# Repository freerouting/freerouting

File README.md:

<h1 align="center">Freerouting</h1>
<h5 align="center">Freerouting is an advanced autorouter for all PCB programs that support the standard Specctra or Electra DSN interface.</h5>

<p align="center">

</p>

<br/>

[**Download installers for Windows, Linux, and macOS here.**](https://github.com/freerouting/freerouting/releases)

> [!IMPORTANT]
> **Project Maintenance and Community Update**
>
> Dear fellow PCB designers and makers,
>
> I have been maintaining Freerouting since January 2020, and first and foremost, a heartfelt thank you to the active members of the community—your passion, contributions, and discussions are truly what keep me motivated.
>
> To be completely candid about my time and the project's funding: in the last 28 days alone, Freerouting had over 332,000 active users, but currently only 4 financial supporters, bringing in just $40 in donations. That is not enough to cover my monthly bills for the AI coding agents that power development, and I will continue paying the difference out of my own pocket.
>
> Because of this, I need to set healthy boundaries and limit my time on the project to around 4 hours per week. Fortunately, Freerouting has matured to a point where it is already good enough for the vast majority of everyday PCB designs. With my limited hours, I will be focusing my energy where it counts most:
>
> - **Pull Requests over Issues:** Reviewing PRs will always take precedence over investigating open issues. Within the codebase, the core routing engine and DRC take priority over integrations and GUI adjustments.
> - **Sponsors and Support:** [Silver and Gold sponsors](https://www.freerouting.app/donate.html) are welcome to contact me directly; I will gladly prioritize their issues and pull requests. Beyond that, I simply do not have the bandwidth for individual technical support or troubleshooting queries.
> - **API Keys:** New API key requests will be reviewed and approved once a week after I manually check the applicants.
> - **Releases:** Official releases will be spaced further apart, likely once every 2 to 3 months.
>
> On the bright side, the foundation is solid, and active community involvement can make a huge difference. If you would like to help keep open-source autorouting moving forward, the best ways to get involved are submitting pull requests, sharing reproducible bug reports with sample design files, or [backing the project financially](https://www.freerouting.app/donate.html). I am always excited to review good code and collaborate with fellow engineers.
>
> Warm regards and happy routing,<br/>
> Andras

## Introduction

Freerouting is a versatile PCB autorouter that works with any PCB design software supporting the standard Specctra or Electra DSN interface. It imports `.dsn` files generated by your CAD software and exports routed `.ses` session files.

## Getting started

You can interact with Freerouting using the Graphical User Interface ([GUI](#graphical-user-interface-gui)), the Command Line Interface ([CLI](#command-line-interface-cli)), or the Freerouting [API](#freerouting-api). All interfaces support command-line arguments to set input/output files or modify settings.

Integrations are available with:

- [KiCad](https://www.kicad.org/)
- [Autodesk Fusion](https://www.autodesk.com/products/fusion-360/overview)
- [Target3001!](https://ibfriedrich.com/en/index.html)
- [EasyEDA](https://www.easyeda.com/)
- [tscircuit](https://tscircuit.com/)
- [pcb-rnd](https://www.pcb-rnd.com/)

[Click here for more details](docs/integrations.md).

### Graphical User Interface (GUI)

1) **Launch Freerouting**: Upon launching, you'll see the main interface.

2) **Open Your Design**: Go to `File` > `Open...` and select your `.dsn` input file.

3) **Start Autorouting**: Click the `Magic Wand` icon to begin the autorouting process.

4) **Monitor Progress**: Watch the routing progress visually in the board editor and numerically in the footer.

5) **Completion**: Wait for the autorouter to finish all passes. This may take from a few minutes to several hours.

6) **Save Your Routed Board**: Go to `File` > `Save as...` to save your routed board as a `.ses` file.

### Command Line Interface (CLI)

When using the CLI, you'll work with an input file (e.g., Specctra `.dsn`) exported from your EDA tool. Freerouting will autoroute unconnected nets and save the results for re-import into your EDA (e.g., as a Specctra `.ses` file).

Common command-line arguments:

- `-de [design input file]`: Load a Specctra design file (`.dsn`) at startup.
- `-do [design output file]`: Save a Specctra session file (`.ses`) after routing.
- `-l [language]`: Set the language (e.g., `en` for English, `de` for German).
- `-inc [net class names]`: Ignore specified net classes during routing.
- `-help`: Display help information.

**Example Command:**

```bash
java -jar path/to/freerouting.jar -de MyBoard.dsn -do MyBoard.ses -inc GND,VCC
```

Download the latest `freerouting-<version>.jar` from the [Releases page](https://github.com/freerouting/freerouting/releases) and substitute its path above.

This command routes `MyBoard.dsn`, ignores the `GND` and `VCC` net classes, and outputs `MyBoard.ses`.

For more details (including headless mode), see the [CLI documentation](docs/command_line_arguments.md).

### Freerouting API

Freerouting offers public API endpoints for PCB routing. The API root is `https://api.freerouting.app/v1`. Check the service status at [`/system/status`](https://api.freerouting.app/v1/system/status).

To access full functionality, request access on the [Freerouting website](https://www.freerouting.app/).

Please note that the Freerouting API and [its documentation](docs/API/API_v1.md) are in beta and may change.

The official Freerouting client SDK currently supports **Python** (maintained in the separate [`freerouting-python-client`](https://github.com/freerouting/freerouting-python-client) repository; install the latest release with `pip install freerouting-client`). This repository also provides OpenAPI-based SDK generation scripts in `scripts/sdk/` for JavaScript, C#, and C++ scaffolding, including `scripts/sdk/regenerate-all.ps1` for one-command scaffold refreshes.

You can also **self-host the Freerouting API** on your own machine or server. See the [Self-Hosting Guide](docs/self-hosting.md) for step-by-step instructions using Docker or a plain Java JRE.

### Model Context Protocol (MCP)

Freerouting supports the Model Context Protocol (MCP) to integrate directly with AI coding assistants (like Cursor, Cline, or Claude Desktop), allowing the AI to query system status and auto-route boards on your behalf.
- **Online Quick Start (Public API)**: Runs instantly via [`npx -y @freerouting/freerouting-mcp-server`](https://www.npmjs.com/package/@freerouting/freerouting-mcp-server) (always fetches the latest release) without requiring a local Java installation.
- **Offline Mode (Local Executable)**: Runs the entire routing engine locally on your machine for complete privacy.

See the [MCP Guide](docs/API/MCP.md) for detailed configuration steps.

## Running Freerouting using Java JRE

Installers are available for Windows x64, Linux x64, and macOS. For other systems, you can run the platform-independent `.jar` file if you have Java JRE installed.

**Steps:**

1. **Download the JAR File**: Get the latest `.jar` from the [Releases page](https://github.com/freerouting/freerouting/releases).

2. **Install Java JRE**: Download and install [Java JRE](https://adoptium.net/temurin/releases/).

   - Choose your operating system and architecture.
   - Select `JRE` as the package type.
   - Choose version `25`.

3. **Run Freerouting**:

   ```bash
   java -jar path/to/freerouting.jar
   ```

   Use the latest `freerouting-<version>.jar` from the [Releases page](https://github.com/freerouting/freerouting/releases).

   **Note for macOS Users**: Launch Freerouting from the Terminal; starting from Finder is not supported.

## Docker Image on GitHub Container Registry (GHCR)

Freerouting Docker images for stable releases (`latest` and version tags) and development (`nightly`) builds are available from [ghcr.io/freerouting/freerouting](https://ghcr.io/freerouting/freerouting). **Prefer the `latest` tag** unless you need a pinned version for reproducibility. The image is a multi-platform manifest supporting:

- `linux/amd64` — x86-64 servers, PCs, most cloud VMs
- `linux/arm64` — Apple Silicon, AWS Graviton, Raspberry Pi 4/5 with 64-bit OS
- `linux/arm/v7` — Raspberry Pi 2/3/4 with 32-bit OS, Umbrel, CasaOS, and other ARMv7 home-server stacks

Docker automatically selects the correct variant for your hardware. For full setup instructions — including Docker Compose examples, network configuration, and running without Docker — see the **[Self-Hosting Guide](docs/self-hosting.md)**.

## Contributing

I ❤️ all contributors — this project wouldn't be possible without you!

- **Report Issues**: Found a bug or have an idea? Open an [issue](https://github.com/freerouting/freerouting/issues).
- **Contribute Code**: Submit fixes and enhancements via [pull requests](https://github.com/freerouting/freerouting/pulls).
- **Guidelines**: Check out the [Contribution Guide](docs/CONTRIBUTING.md) and [Developer Documentation](docs/developer.md). Router and optimizer board scores are documented in [docs/scoring.md](docs/scoring.md).

## Connect & Community

I'd love to stay connected! You can reach out, follow updates, or join discussions through any of these channels:

- **Freerouting on X (Twitter)**: [@freeroutingPCB](https://x.com/freeroutingPCB)
- **Personal X (Twitter)**: [@andrasfuchs](https://x.com/andrasfuchs)
- **LinkedIn**: [Andras Fuchs](https://www.linkedin.com/in/andrasfuchs/)
- **Email**: [info@freerouting.app](mailto:info@freerouting.app)
- **Discussions**: [GitHub Discussions](https://github.com/freerouting/freerouting/discussions)

## 🙏 Support the Project

**If you'd like to support the project financially, [please consider sponsoring the project](https://github.com/sponsors/andrasfuchs).**

**Every contribution, no matter how small, is greatly appreciated!**

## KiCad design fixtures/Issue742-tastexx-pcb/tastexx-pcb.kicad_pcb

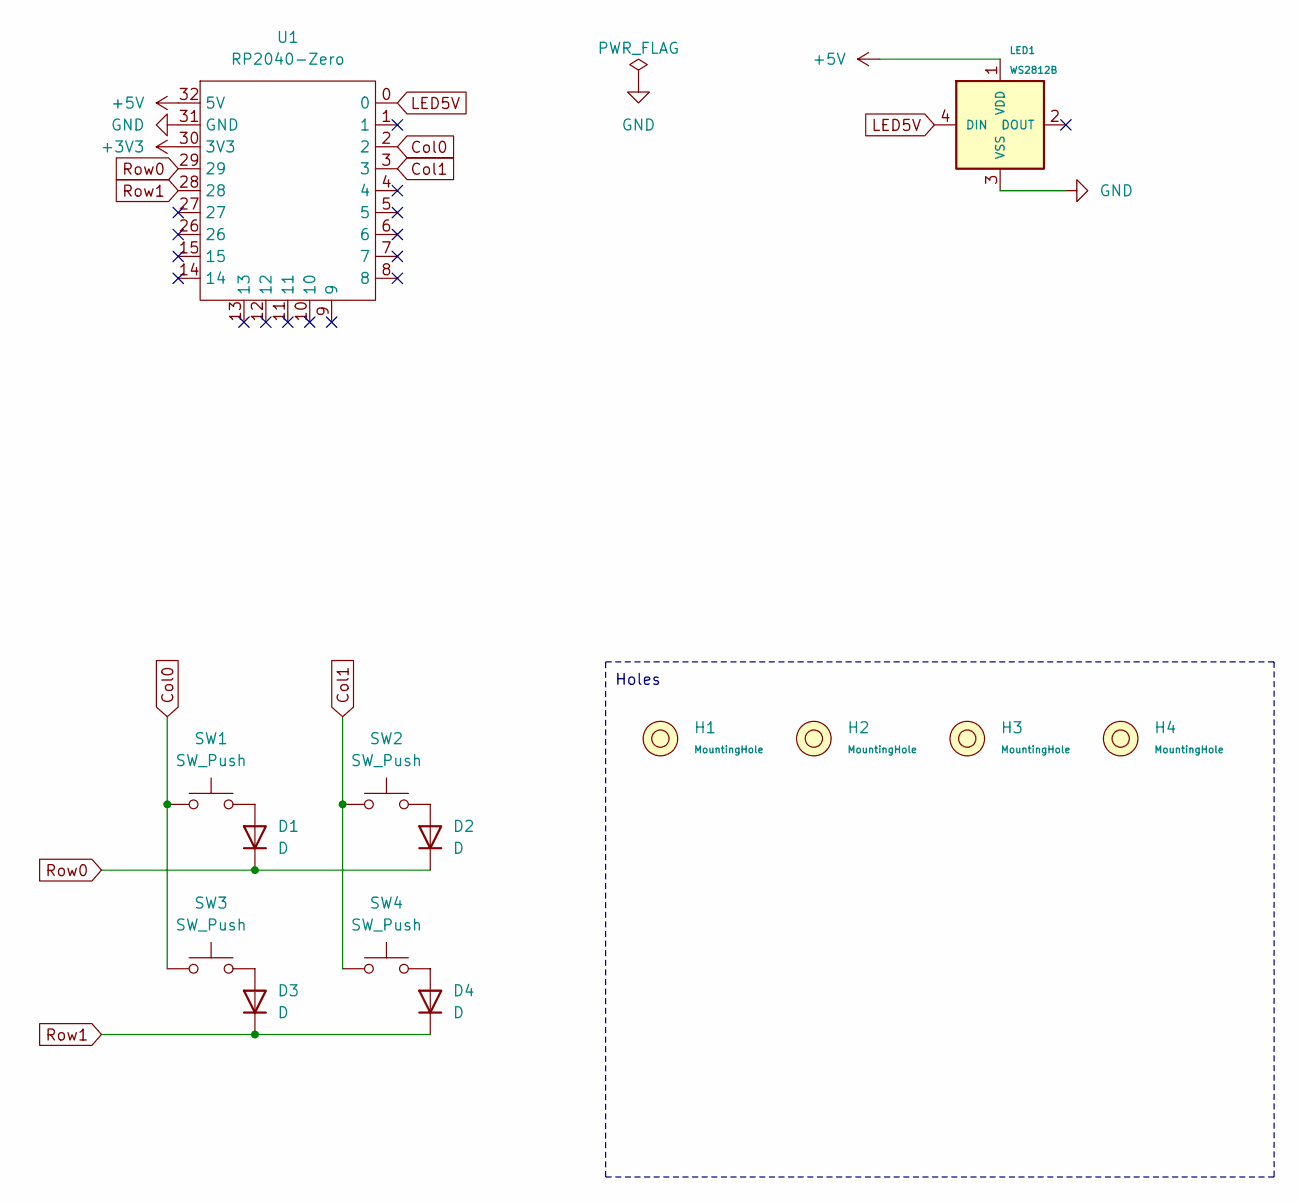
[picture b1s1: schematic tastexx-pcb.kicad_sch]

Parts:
D1, D2, D3, D4: D; Diode_SMD
H1, H2, H3, H4: MountingHole; M2_ScrewHole_EdgeCuts
LED1: WS2812B; LED_WS2812B_UG
SW1, SW2, SW3, SW4: SW_Push; CherryMX_GLP3.0_Hotswap_1u
U1: RP2040-Zero

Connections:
+3V3: U1.30 (3V3)
+5V: LED1.1 (VDD), U1.32 (5V)
Col0: SW1.1, SW3.1, U1.2
Col1: SW2.1, SW4.1, U1.3
GND: LED1.3 (VSS), U1.31 (GND)
LED5V: LED1.4 (DIN), U1.0
unnamed: D1.2 (A), SW1.2
unnamed: D2.2 (A), SW2.2
unnamed: D3.2 (A), SW3.2
unnamed: D4.2 (A), SW4.2
Row0: D1.1 (K), D2.1 (K), U1.29
Row1: D3.1 (K), D4.1 (K), U1.28

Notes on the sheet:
Holes

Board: 2 copper layers, 14 parts (0 on the bottom side), 11 nets, no tracks yet.

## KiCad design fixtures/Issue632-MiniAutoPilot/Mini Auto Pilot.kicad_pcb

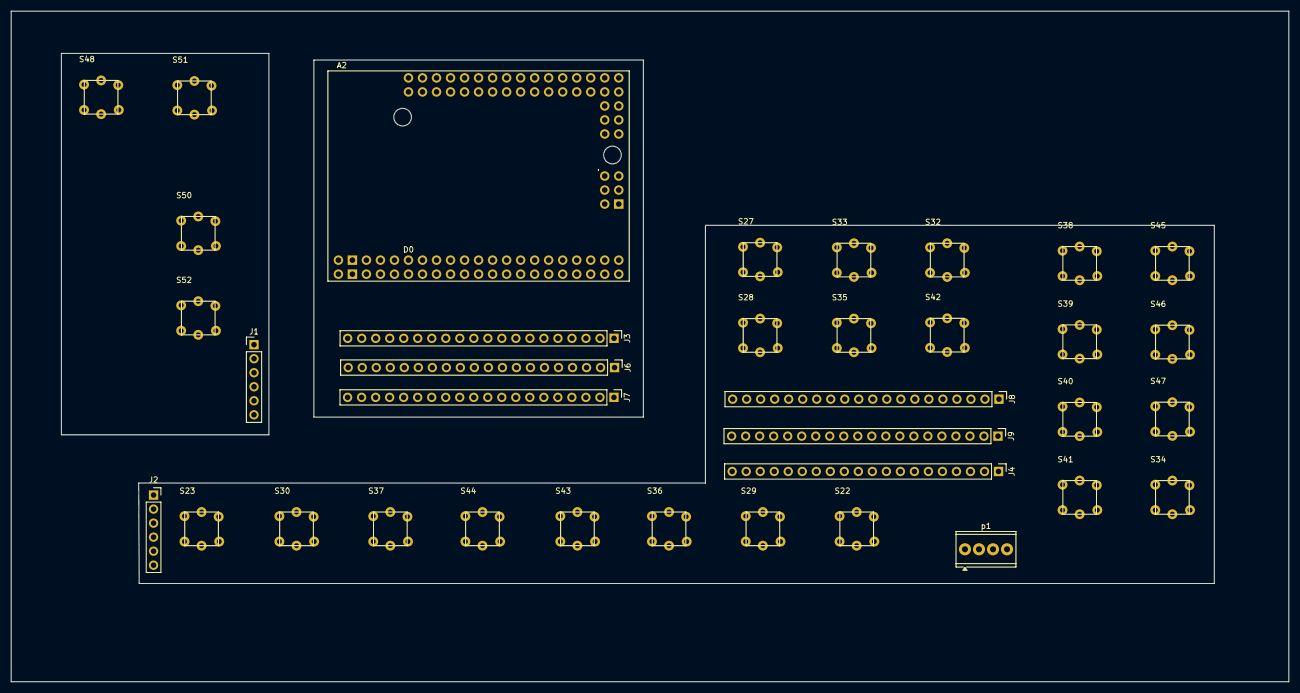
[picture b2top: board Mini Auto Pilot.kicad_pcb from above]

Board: 2 copper layers, 231.5 x 121.5 mm, 36 parts (0 on the bottom side), 93 nets, no tracks yet.

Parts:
A2: Clone_Mega2560_Pro_Socket
J1: PINHD_1x6_Male; PinHeader_1x06_P2.54mm_Vertical
J2: PINHD_1x6_Female; PinSocket_1x06_P2.54mm_Vertical
J3: PINHD_1x20_Female_1-20; PinHeader_1x20_P2.54mm_Vertical_1-20
J4: PINHD_1x20_Male_41-60; PinHeader_1x20_P2.54mm_Vertical_41-60
J6: PINHD_1x20_Female_21-40; PinHeader_1x20_P2.54mm_Vertical_21-40
J7: PINHD_1x20_Female_41-60; PinHeader_1x20_P2.54mm_Vertical_41-60
J8: PINHD_1x20_Male_1-20; PinHeader_1x20_P2.54mm_Vertical_1-20
J9: PINHD_1x20_Male_21-40; PinHeader_1x20_P2.54mm_Vertical_21-40
S22, S23, S27, S28, S29, S30, S32, S33, S34, S35, S36, S37, S38, S39, S40, S41, S42, S43, S44, S45, S46, S47, S48, S50, S51, S52: TL3240F160BT; Mini Switch LED
p1: Screw_Terminal_4_P2.54mm; TerminalBlock_Phoenix_MPT-0,5-4-2.54_1x04_P2.54mm_Horizontal

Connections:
/6pin-1: J2.1, J9.28
/6pin-2: J2.2, J9.34
/6pin-3: J2.3, J4.43
/6pin-4: J2.4, J4.44
/6pin-5: J2.5, J4.56, p1.2
/6pin-6: J2.6, J4.57
/Arduino/3.3V: A2.3V31 (3.3V), J7.55
/Arduino/5V: A2.5V1 (5V), J7.56
/Arduino/D1: A2.D1 (D1/TX0), J3.1
/Arduino/D2: A2.D2 (D2_INT0), J3.2
/Arduino/D3: A2.D3 (D3_INT1), J3.3
/Arduino/D4: A2.D4, J3.4
/Arduino/D5: A2.D5, J3.5
/Arduino/D6: A2.D6, J3.6
/Arduino/D7: A2.D7, J3.7
/Arduino/D8: A2.D8, J3.8
/Arduino/D9: A2.D9, J3.9
/Arduino/D10: A2.D10, J3.10
/Arduino/D11: A2.D11, J3.11
/Arduino/D12: A2.D12, J3.12
/Arduino/D13: A2.D13, J3.13
/Arduino/D14: A2.D14 (D14/TX3), J3.14
/Arduino/D15: A2.D15 (D15/RX3), J3.15
/Arduino/D16: A2.D16 (D16/TX2), J3.16
/Arduino/D17: A2.D17 (D17/RX2), J3.17
/Arduino/D18: A2.D18 (D18/TX1), J3.18
/Arduino/D19: A2.D19 (D19/RX1), J3.19
/Arduino/D20: A2.D20 (D20/SDA), J3.20
/Arduino/D21: A2.D21 (D21/SCL), J6.21
/Arduino/D22: A2.D22, J6.22
/Arduino/D23: A2.D23, J6.23
/Arduino/D24: A2.D24, J6.24
/Arduino/D25: A2.D25, J6.25
/Arduino/D26: A2.D26, J6.26
/Arduino/D27: A2.D27, J6.27
/Arduino/D28: A2.D28, J6.28
/Arduino/D29: A2.D29, J6.29
/Arduino/D30: A2.D30, J6.30
/Arduino/D31: A2.D31, J6.31
/Arduino/D32: A2.D32, J6.32
/Arduino/D33: A2.D33, J6.33
/Arduino/D34: A2.D34, J6.34
/Arduino/D35: A2.D35, J6.35
/Arduino/D36: A2.D36, J6.36
/Arduino/D37: A2.D37, J6.37
/Arduino/D38: A2.D38, J6.38
/Arduino/D39: A2.D39, J6.39
/Arduino/D40: A2.D40, J6.40
/Arduino/D41: A2.D41, J7.41
/Arduino/D42: A2.D42, J7.42
/Arduino/D43: A2.D43, J7.43
/Arduino/D44: A2.D44, J7.44
/Arduino/D45: A2.D45, J7.45
/Arduino/D46: A2.D46, J7.46
/Arduino/D47: A2.D47, J7.47
/Arduino/D48: A2.D48, J7.48
/Arduino/D49: A2.D49, J7.49
/Arduino/D50: A2.D50 (D50_MISO), J7.50
/Arduino/D51: A2.D51 (D51_MOSI), J7.51
/Arduino/D52: A2.D52 (D52_SCK), J7.52
/Arduino/D53: A2.D53 (D53_CS), J7.53
/Arduino/GND: A2.GND2 (GND), J7.54
/D4: J8.4, S43.1
/D5: J8.5, S44.1
/D6: J8.6, S45.1
/D7: J8.7, S46.1
/D8: J8.8, S47.1
/D10: J8.10, S41.1
/D11: J8.11, S39.1
/D14: J8.14, S42.1
/D15: J8.15, S27.1
/D16: J8.16, S23.1
/D17: J8.17, S22.1
/D18: J8.18, S29.1
/D19: J8.19, S28.1
/D20: J8.20, p1.4
/D22: J9.22, S30.1
/D24: J9.24, S40.1
/D25: J9.25, S37.1
/D26: J9.26, S32.1
/D27: J9.27, S33.1
/D29: J9.29, S34.1
/D30: J9.30, S35.1
/D31: J9.31, S36.1
/left buttons/6Pin-1: J1.1, S50.1
/left buttons/6Pin-2: J1.2, S51.1
/left buttons/6Pin-3: J1.3, S52.1
/left buttons/6Pin-4: J1.4, S48.1
/left buttons/6Pin-5: J1.5, S48.5, S50.5, S51.5, S52.5
/left buttons/6Pin-6: J1.6, S48.3, S48.6, S50.3, S50.6, S51.3, S51.6, S52.3, S52.6
GND: S22.3, S22.6, S23.3, S23.6, S27.3, S27.6, S28.3, S28.6, S29.3, S29.6, S30.3, S30.6, S32.3, S32.6, S33.3, S33.6, S34.3, S34.6, S35.3, S35.6, S36.3, S36.6, S37.3, S37.6, S38.3, S38.6, S39.3, S39.6, S40.3, S40.6, S41.3, S41.6, S42.3, S42.6, S43.3, S43.6, S44.3, S44.6, S45.3, S45.6, S46.3, S46.6, S47.3, S47.6, p1.1
unnamed: J9.21, p1.3
unnamed: S22.5, S23.5, S27.5, S28.5, S29.5, S30.5, S32.5, S33.5, S34.5, S35.5, S36.5, S37.5, S38.5, S39.5, S40.5, S41.5, S42.5, S43.5, S44.5, S45.5, S46.5, S47.5

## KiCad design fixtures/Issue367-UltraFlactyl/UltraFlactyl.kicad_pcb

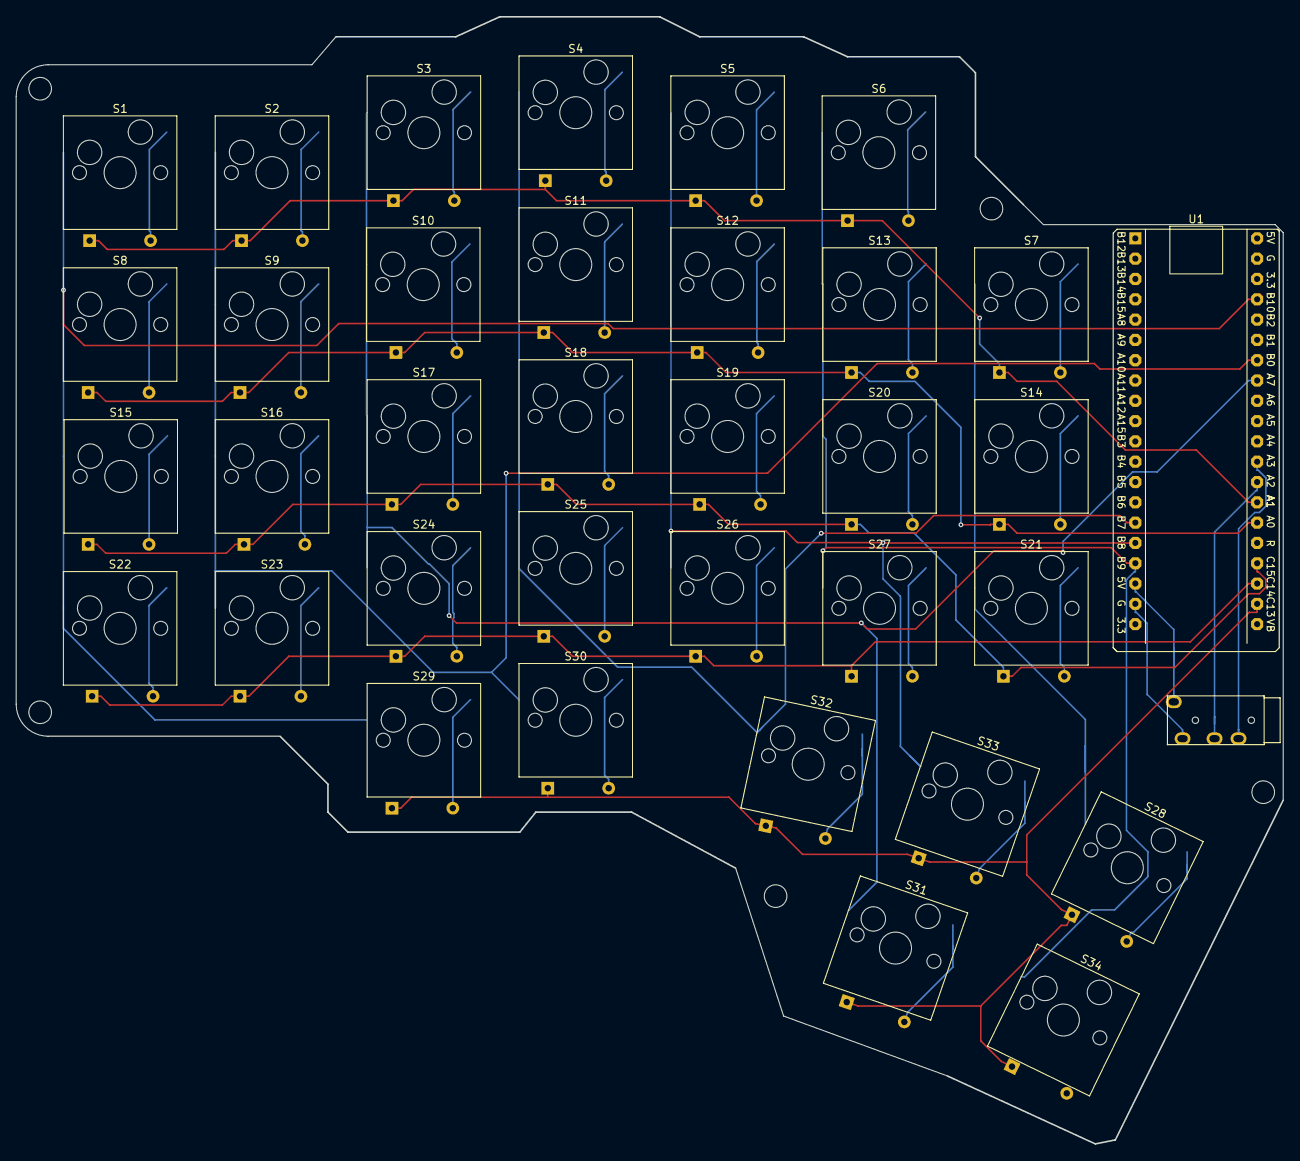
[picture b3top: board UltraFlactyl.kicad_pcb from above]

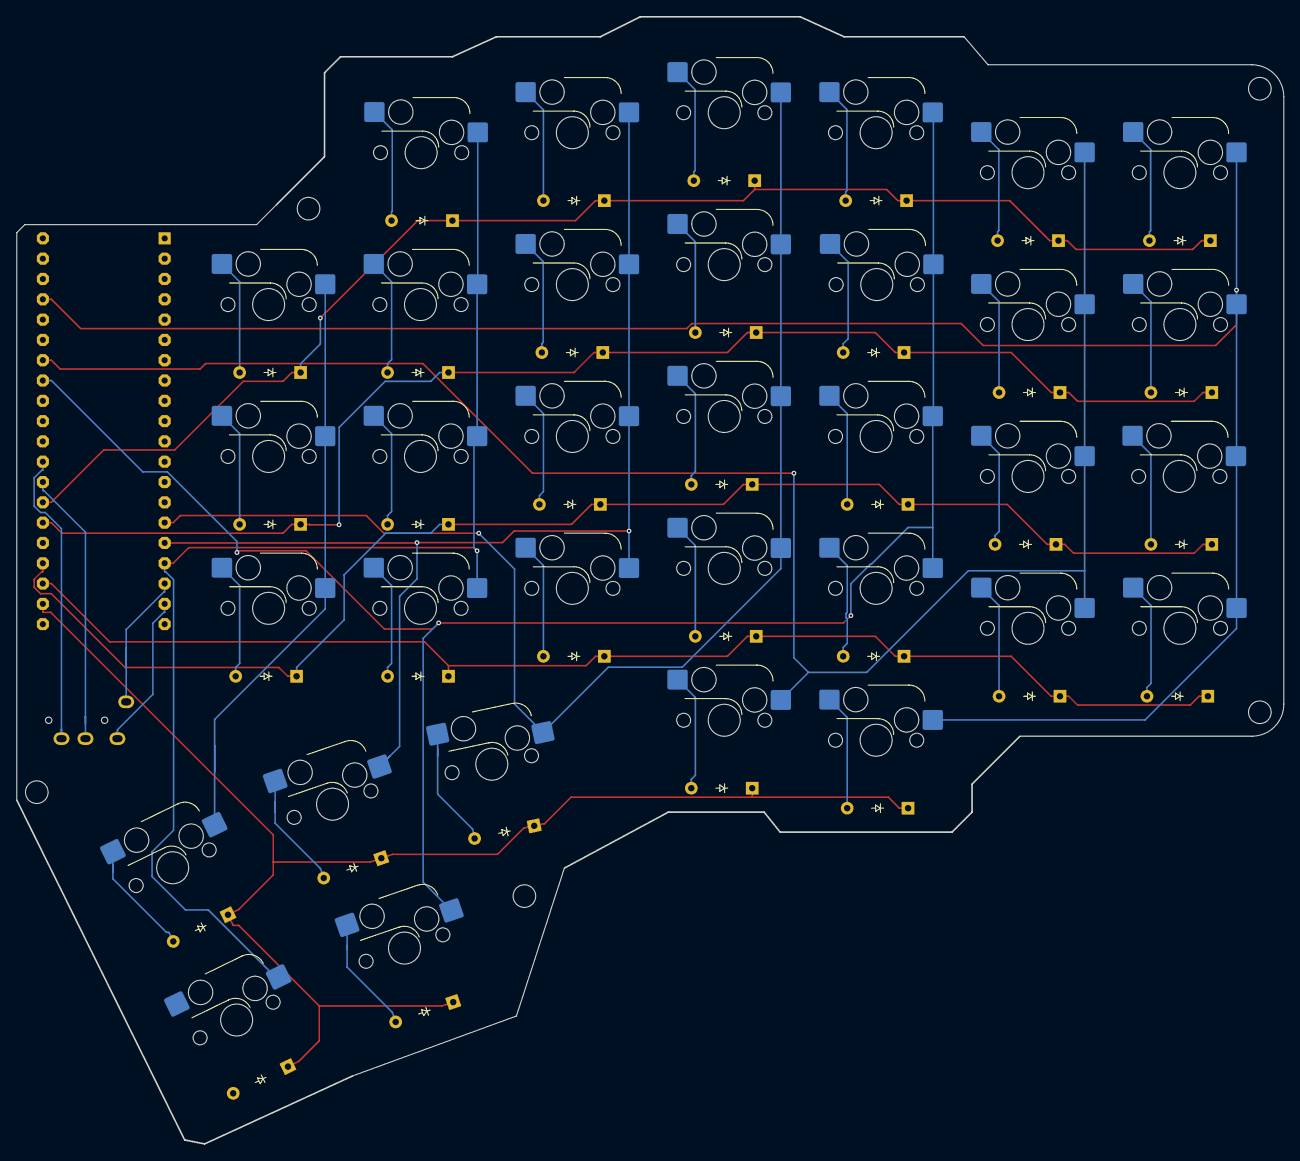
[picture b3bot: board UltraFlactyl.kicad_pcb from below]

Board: 2 copper layers, 158.5 x 141.0 mm, 70 parts (34 on the bottom side), 50 nets.

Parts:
D1, D2, D3, D4, D5, D6, D7, D8, D9, D10, D11, D12, D13, D14, D15, D16, D17, D18, D19, D20, D21, D22, D23, D24, D25, D26, D27, D28, D29, D30, D31, D32, D33, D34: Diode; Diode_DO-35
S1, S2, S3, S4, S5, S6, S7, S8, S9, S10, S11, S12, S13, S14, S15, S16, S17, S18, S19, S20, S21, S22, S23, S24, S25, S26, S27, S28, S29, S30, S31, S32, S33, S34: Keyswitch; Hotswap_MX_1.00u
U1: STM32F411 BlackPill; STM32F411_Black_Pill
U2: TRRS; TRRS_PJ-320A

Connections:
C1: S1.1, S8.1, S15.1, S22.1, S29.1, U1.37 (B10)
C2: S2.1, S9.1, S16.1, S23.1, S30.1, U1.34 (B0)
C3: S3.1, S10.1, S17.1, S24.1, S31.1, U1.33 (A7)
C4: S4.1, S11.1, S18.1, S25.1, S32.1, U1.15 (B7)
C5: S5.1, S12.1, S19.1, S26.1, S33.1, U1.16 (B8)
C6: S6.1, S13.1, S20.1, S27.1, S34.1, U1.17 (B9)
C7: S7.1, S14.1, S21.1, S28.1
GND: U1.19 (G), U2.2 (TIP)
unnamed: D1.2 (A), S1.2
unnamed: D2.2 (A), S2.2
unnamed: D3.2 (A), S3.2
unnamed: D4.2 (A), S4.2
unnamed: D5.2 (A), S5.2
unnamed: D6.2 (A), S6.2
unnamed: D7.2 (A), S7.2
unnamed: D8.2 (A), S8.2
unnamed: D9.2 (A), S9.2
unnamed: D10.2 (A), S10.2
unnamed: D11.2 (A), S11.2
unnamed: D12.2 (A), S12.2
unnamed: D13.2 (A), S13.2
unnamed: D14.2 (A), S14.2
unnamed: D15.2 (A), S15.2
unnamed: D16.2 (A), S16.2
unnamed: D17.2 (A), S17.2
unnamed: D18.2 (A), S18.2
unnamed: D19.2 (A), S19.2
unnamed: D20.2 (A), S20.2
unnamed: D21.2 (A), S21.2
unnamed: D22.2 (A), S22.2
unnamed: D23.2 (A), S23.2
unnamed: D24.2 (A), S24.2
unnamed: D25.2 (A), S25.2
unnamed: D26.2 (A), S26.2
unnamed: D27.2 (A), S27.2
unnamed: D28.2 (A), S28.2
unnamed: D29.2 (A), S29.2
unnamed: D30.2 (A), S30.2
unnamed: D31.2 (A), S31.2
unnamed: D32.2 (A), S32.2
unnamed: D33.2 (A), S33.2
unnamed: D34.2 (A), S34.2
R1: D1.1 (K), D2.1 (K), D3.1 (K), D4.1 (K), D5.1 (K), D6.1 (K), D7.1 (K), U1.27 (A1)
R2: D8.1 (K), D9.1 (K), D10.1 (K), D11.1 (K), D12.1 (K), D13.1 (K), D14.1 (K), U1.26 (A0)
R3: D15.1 (K), D16.1 (K), D17.1 (K), D18.1 (K), D19.1 (K), D20.1 (K), D21.1 (K), U1.24 (C15)
R4: D22.1 (K), D23.1 (K), D24.1 (K), D25.1 (K), D26.1 (K), D27.1 (K), U1.23 (C14)
R5: D28.1 (K), D29.1 (K), D30.1 (K), D31.1 (K), D32.1 (K), D33.1 (K), D34.1 (K), U1.22 (C13)
RX: U1.28 (A2), U2.3 (RING1)
TX: U1.29 (A3), U2.4 (RING2)
VCC: U1.18 (5V), U2.1 (SLEEVE)

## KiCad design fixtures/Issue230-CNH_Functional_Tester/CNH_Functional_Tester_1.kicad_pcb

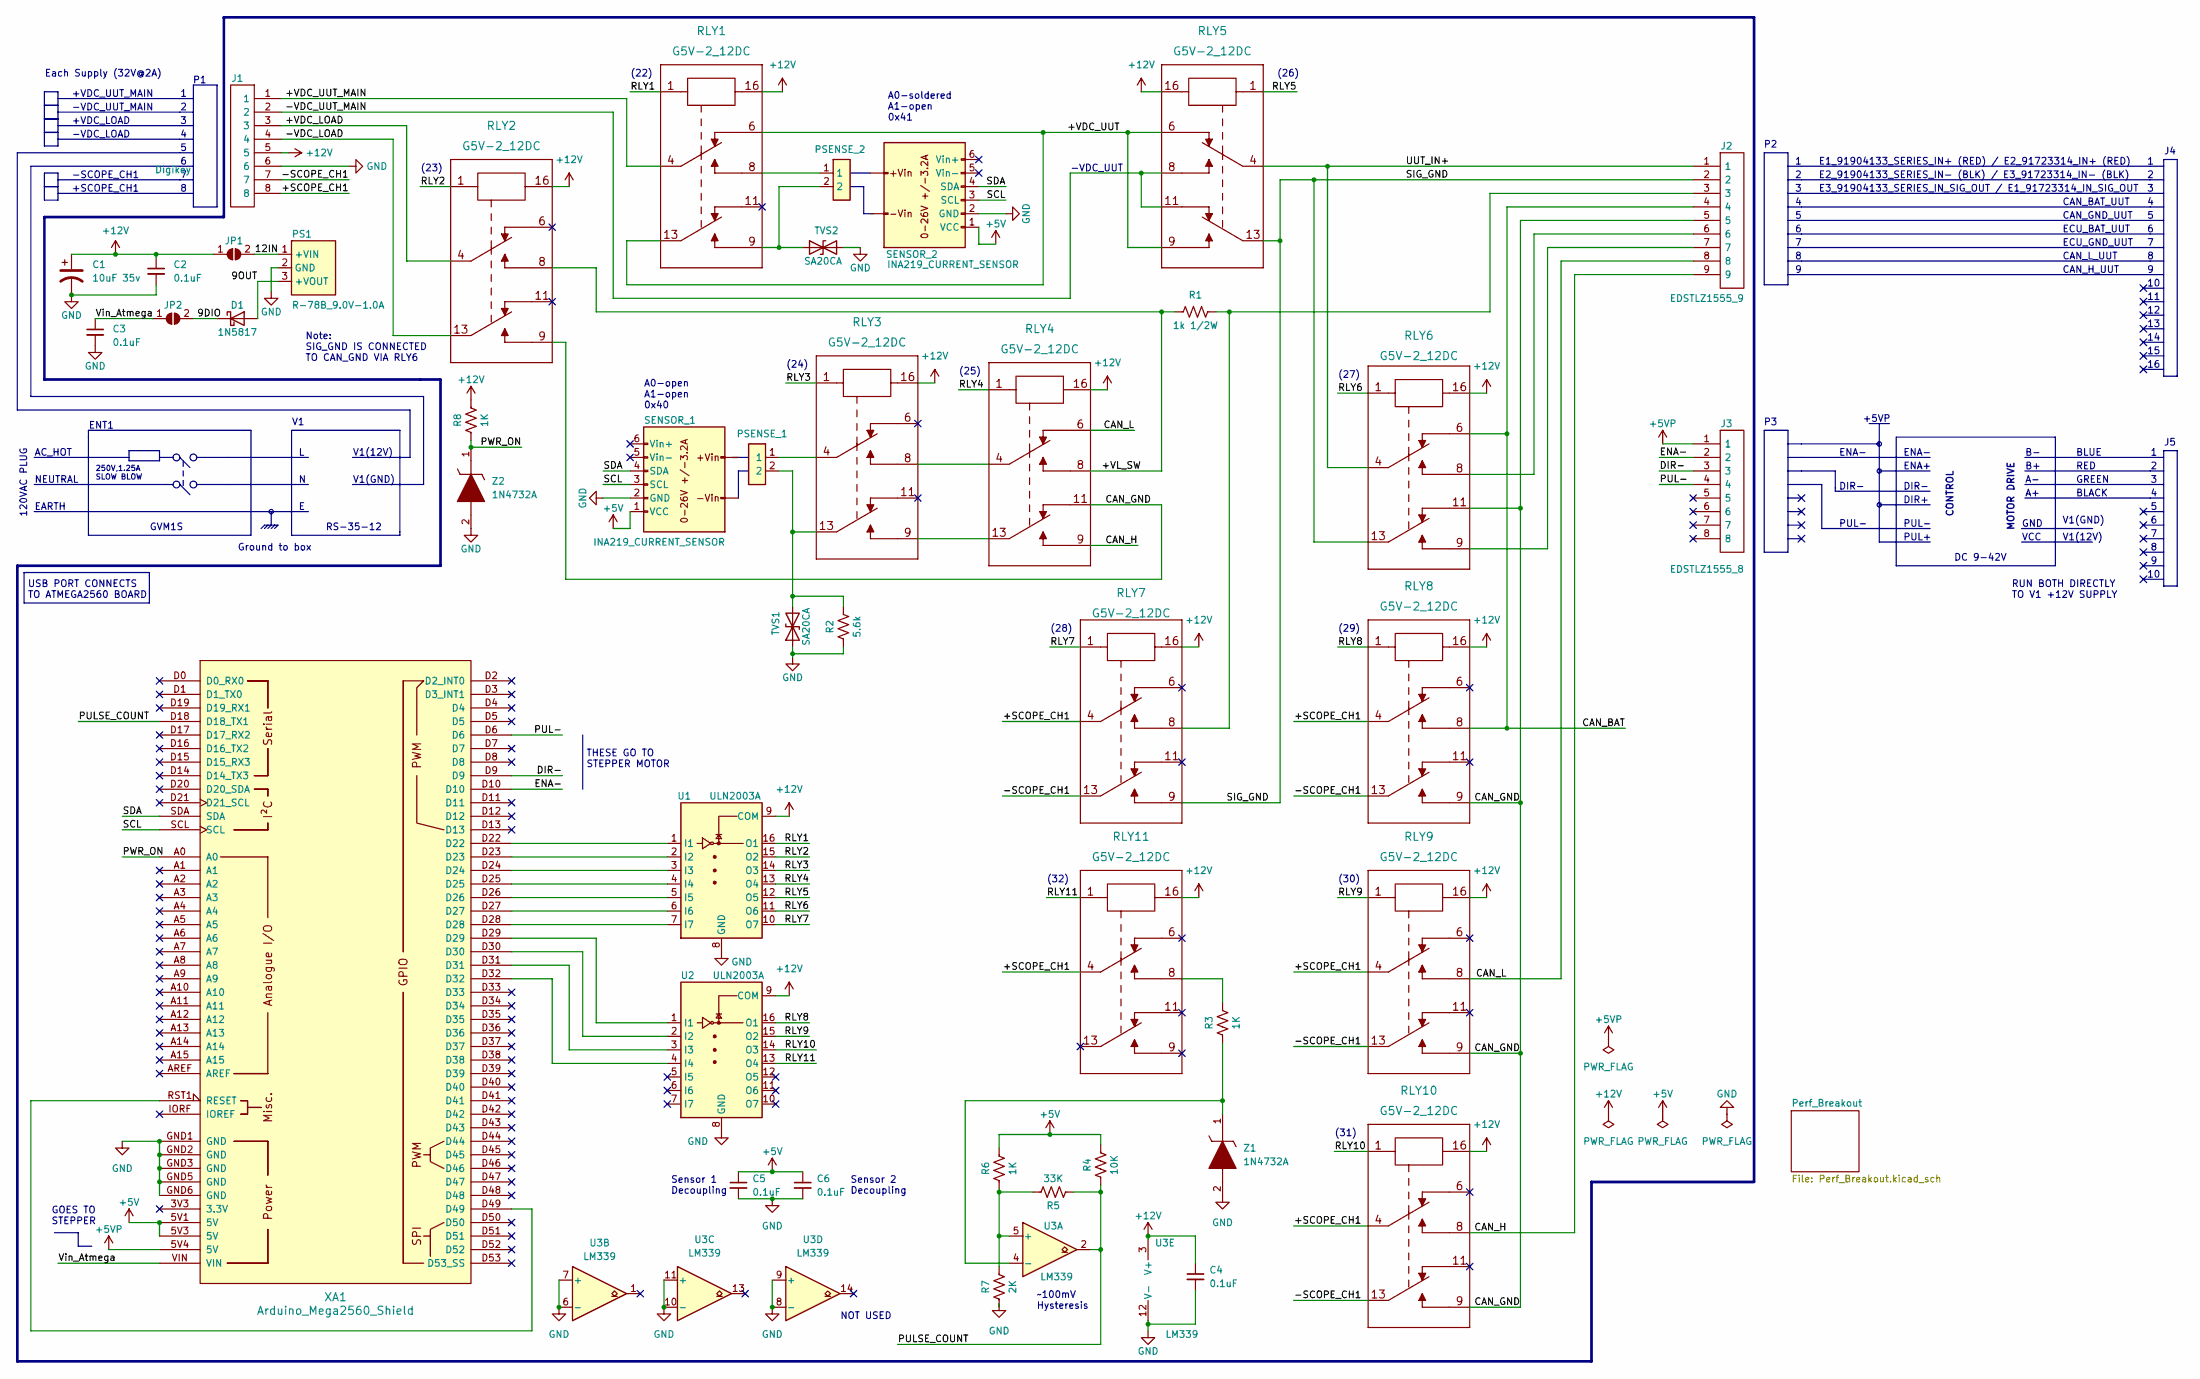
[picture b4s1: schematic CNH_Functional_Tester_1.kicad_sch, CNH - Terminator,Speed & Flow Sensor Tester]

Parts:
C1: 10uF 35v; CP_Radial_D5.0mm_P2.00mm
C2, C3, C4, C5, C6: 0.1uF; C_Axial_L170mil_D100mil_P370mil_Horizontal
D1: 1N5817; D_DO-41_SOD81_P10.16mm_Horizontal
J1, J3: EDSTLZ1555_8; CONN-TH_EDSTLZ1555-8; Manufacturer_Part_Number EDSTLZ1555/8
J2: EDSTLZ1555_9; CONN-TH_EDSTLZ1555-9; Manufacturer_Part_Number EDSTLZ1555/8
JP1, JP2: SolderJumper_2_Open; SolderJumper-2_P1.3mm_Open_RoundedPad1.0x1.5mm
PS1: R-78B_9.0V-1.0A; R78_9V_1A_SIP_TH; Manufacturer_Part_Number R-78B9.0-1.0
PSENSE_1, PSENSE_2: 1727010_2PIN_3.81mm_CONN; Mouser Part Number 651-1727010
R1: 1k 1/2W; R_Axial_DIN0207_L6.3mm_D2.5mm_P11.43mm_Horizontal_0.25W
R2: 5.6k; R_Axial_DIN0207_L6.3mm_D2.5mm_P11.43mm_Horizontal_0.25W
R3, R6, R8: 1K; R_Axial_DIN0207_L6.3mm_D2.5mm_P11.43mm_Horizontal_0.25W
R4: 10K; R_Axial_DIN0207_L6.3mm_D2.5mm_P11.43mm_Horizontal_0.25W
R5: 33K; R_Axial_DIN0207_L6.3mm_D2.5mm_P11.43mm_Horizontal_0.25W
R7: 2K; R_Axial_DIN0207_L6.3mm_D2.5mm_P11.43mm_Horizontal_0.25W
RLY1, RLY2, RLY3, RLY4, RLY5, RLY6, RLY7, RLY8, RLY9, RLY10, RLY11: G5V-2_12DC; Relay_DPDT_Omron_G5V-2
SENSOR_1, SENSOR_2: INA219_CURRENT_SENSOR
TVS1, TVS2: SA20CA; SA20CA_P12.70mm_Horizontal
U1, U2: ULN2003A; DIP-16_W7.62mm_LongPads
U3: LM339; DIP-14_W7.62mm_LongPads
XA1: Arduino_Mega2560_Shield
Z1, Z2: 1N4732A; D_DO-41_SOD81_P10.16mm_Horizontal; Mouser Part Number 512-1N4732A

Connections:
+5V: C5.1, C6.1, R4.1, R6.1, SENSOR_1.1 (VCC), SENSOR_2.1 (VCC), XA1.5V1 (5V), XA1.5V3 (5V); also elsewhere on the board
+5VP: J3.1, XA1.5V4 (5V)
+12V: C1.1, C2.1, C4.1, J1.5, JP1.1 (A), R8.1, RLY1.16, RLY2.16, RLY3.16, RLY4.16, RLY5.16, RLY6.16, RLY7.16, RLY8.16, RLY9.16, RLY10.16, RLY11.16, U1.9 (COM), U2.9 (COM), U3.3 (V+); also elsewhere on the board
/9DIO: D1.1 (K), JP2.2 (B)
/9OUT: D1.2 (A), PS1.3 (+VOUT)
/12IN: JP1.2 (B), PS1.1 (+VIN)
/+SCOPE_CH1: J1.8, RLY7.4, RLY8.4, RLY9.4, RLY10.4, RLY11.4
/+VDC_LOAD: J1.3, RLY2.4
/+VDC_UUT: RLY1.6, RLY1.13, RLY5.6, RLY5.9
/+VDC_UUT_MAIN: J1.1, RLY1.4
/+VL_SW: R1.1, RLY2.8, RLY4.8
/-SCOPE_CH1: J1.7, RLY7.13, RLY8.13, RLY9.13, RLY10.13
/-VDC_LOAD: J1.4, RLY2.13
/-VDC_UUT_MAIN: J1.2, RLY5.8, RLY5.11
/CAN_BAT: J2.4, RLY6.6, RLY8.8
/CAN_GND: J2.5, RLY2.9, RLY4.11, RLY6.11, RLY8.9, RLY9.9, RLY10.9
/CAN_H: J2.9, RLY4.9, RLY10.8
/CAN_L: J2.8, RLY4.6, RLY9.8
/DIR-: J3.3, XA1.D9
/ENA-: J3.2, XA1.D10
/PUL-: J3.4, XA1.D6
/PULSE_COUNT: R4.2, R5.2, U3.2, XA1.D18 (D18_TX1)
/PWR_ON: R8.2, XA1.A0, Z2.1
/RLY1: RLY1.1, U1.16 (O1)
/RLY2: RLY2.1, U1.15 (O2)
/RLY3: RLY3.1, U1.14 (O3)
/RLY4: RLY4.1, U1.13 (O4)
/RLY5: RLY5.1, U1.12 (O5)
/RLY6: RLY6.1, U1.11 (O6)
/RLY7: RLY7.1, U1.10 (O7)
/RLY8: RLY8.1, U2.16 (O1)
/RLY9: RLY9.1, U2.15 (O2)
/RLY10: RLY10.1, U2.14 (O3)
/RLY11: RLY11.1, U2.13 (O4)
/SCL: SENSOR_1.3 (SCL), SENSOR_2.3 (SCL), XA1.SCL
/SDA: SENSOR_1.4 (SDA), SENSOR_2.4 (SDA), XA1.SDA
/SIG_GND: J2.2, RLY5.13, RLY6.13, RLY7.9
/UUT_IN+: J2.1, RLY5.4, RLY6.4
/Vin_Atmega: C3.1, JP2.1 (A), XA1.VIN
GND: C1.2, C2.2, C3.2, C4.2, C5.2, C6.2, J1.6, PS1.2 (GND), R2.2, R7.2, SENSOR_1.2 (GND), SENSOR_2.2 (GND), TVS1.1 (A1), TVS2.2 (A2), U1.8 (GND), U2.8 (GND), U3.6 (-), U3.7 (+), U3.8 (-), U3.9 (+), U3.10 (-), U3.11 (+), U3.12 (V-), XA1.GND1 (GND), XA1.GND2 (GND), XA1.GND3 (GND), XA1.GND5 (GND), XA1.GND6 (GND), Z1.2, Z2.2; also elsewhere on the board
unnamed: J2.3, R1.2, RLY7.8
unnamed: J2.6, RLY6.8
unnamed: J2.7, RLY6.9
unnamed: PSENSE_1.1, RLY3.4
unnamed: PSENSE_2.1, RLY1.8
unnamed: R3.1, RLY11.8
unnamed: RLY3.8, RLY4.4
unnamed: RLY3.9, RLY4.13
unnamed: PSENSE_1.2, R2.1, RLY3.13, TVS1.2 (A2)
unnamed: PSENSE_2.2, RLY1.9, TVS2.1 (A1)
unnamed: U1.1 (I1), XA1.D22
unnamed: U1.2 (I2), XA1.D23
unnamed: U1.3 (I3), XA1.D24
unnamed: U1.4 (I4), XA1.D25
unnamed: U1.5 (I5), XA1.D26
unnamed: U1.6 (I6), XA1.D27
unnamed: U1.7 (I7), XA1.D28
unnamed: U2.1 (I1), XA1.D29
unnamed: U2.2 (I2), XA1.D30
unnamed: U2.3 (I3), XA1.D31
unnamed: U2.4 (I4), XA1.D32
unnamed: R5.1, R6.2, R7.1, U3.5 (+)
unnamed: R3.2, U3.4 (-), Z1.1
unnamed: XA1.D49, XA1.RST1 (RESET)

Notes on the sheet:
+5VP
PUL-
(28)
DIR-
-VDC_UUT
ECU_BAT_UUT
Ground to box
CAN_L_UUT
GVM1S
MOTOR DRIVE
ECU_GND_UUT
CAN_H_UUT
A0-open A1-open 0x40
RUN BOTH DIRECTLY TO V1 +12V SUPPLY
PUL+
V1(GND)
ENA-
(25)
DC 9-42V
(31)
~100mV Hysteresis
+SCOPE_CH1
-SCOPE_CH1
+VDC_UUT_MAIN
Each Supply (32V@2A)
GOES TO STEPPER
AC_HOT
NOT USED
-VDC_LOAD
ENT1
Sensor 1 Decoupling
-VDC_UUT_MAIN
CONTROL
(23)
120VAC PLUG
(22)
E1_91904133_SERIES_IN+ (RED) / E2_91723314_IN+ (RED)
(26)
VCC
BLACK

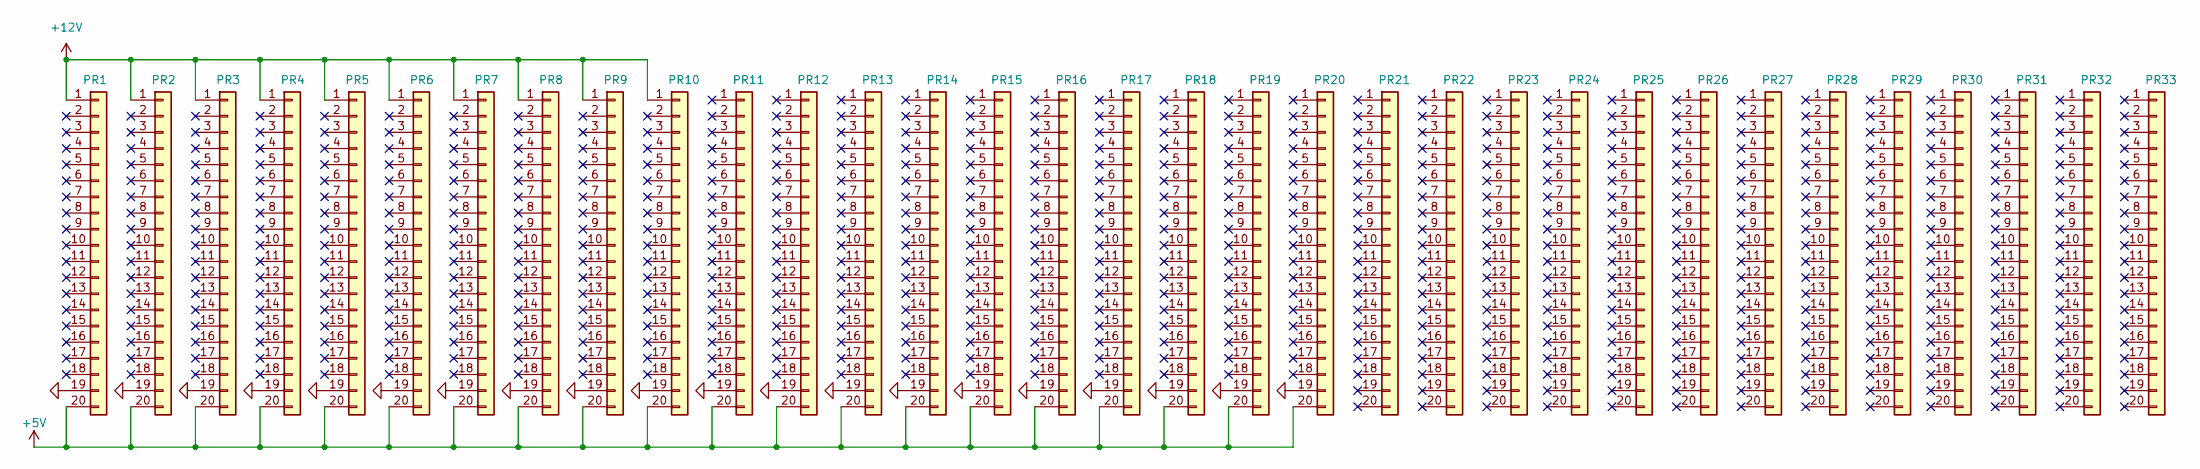
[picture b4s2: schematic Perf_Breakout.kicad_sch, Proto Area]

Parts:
PR1, PR2, PR3, PR4, PR5, PR6, PR7, PR8, PR9, PR10, PR11, PR12, PR13, PR14, PR15, PR16, PR17, PR18, PR19, PR20, PR21, PR22, PR23, PR24, PR25, PR26, PR27, PR28, PR29, PR30, PR31, PR32, PR33: Conn_01x20_Perf; SIP-20_PERF

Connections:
+5V: PR1.20, PR2.20, PR3.20, PR4.20, PR5.20, PR6.20, PR7.20, PR8.20, PR9.20, PR10.20, PR11.20, PR12.20, PR13.20, PR14.20, PR15.20, PR16.20, PR17.20, PR18.20, PR19.20, PR20.20; also elsewhere on the board
+12V: PR1.1, PR2.1, PR3.1, PR4.1, PR5.1, PR6.1, PR7.1, PR8.1, PR9.1, PR10.1; also elsewhere on the board
GND: PR1.19, PR2.19, PR3.19, PR4.19, PR5.19, PR6.19, PR7.19, PR8.19, PR9.19, PR10.19, PR11.19, PR12.19, PR13.19, PR14.19, PR15.19, PR16.19, PR17.19, PR18.19, PR19.19, PR20.19; also elsewhere on the board

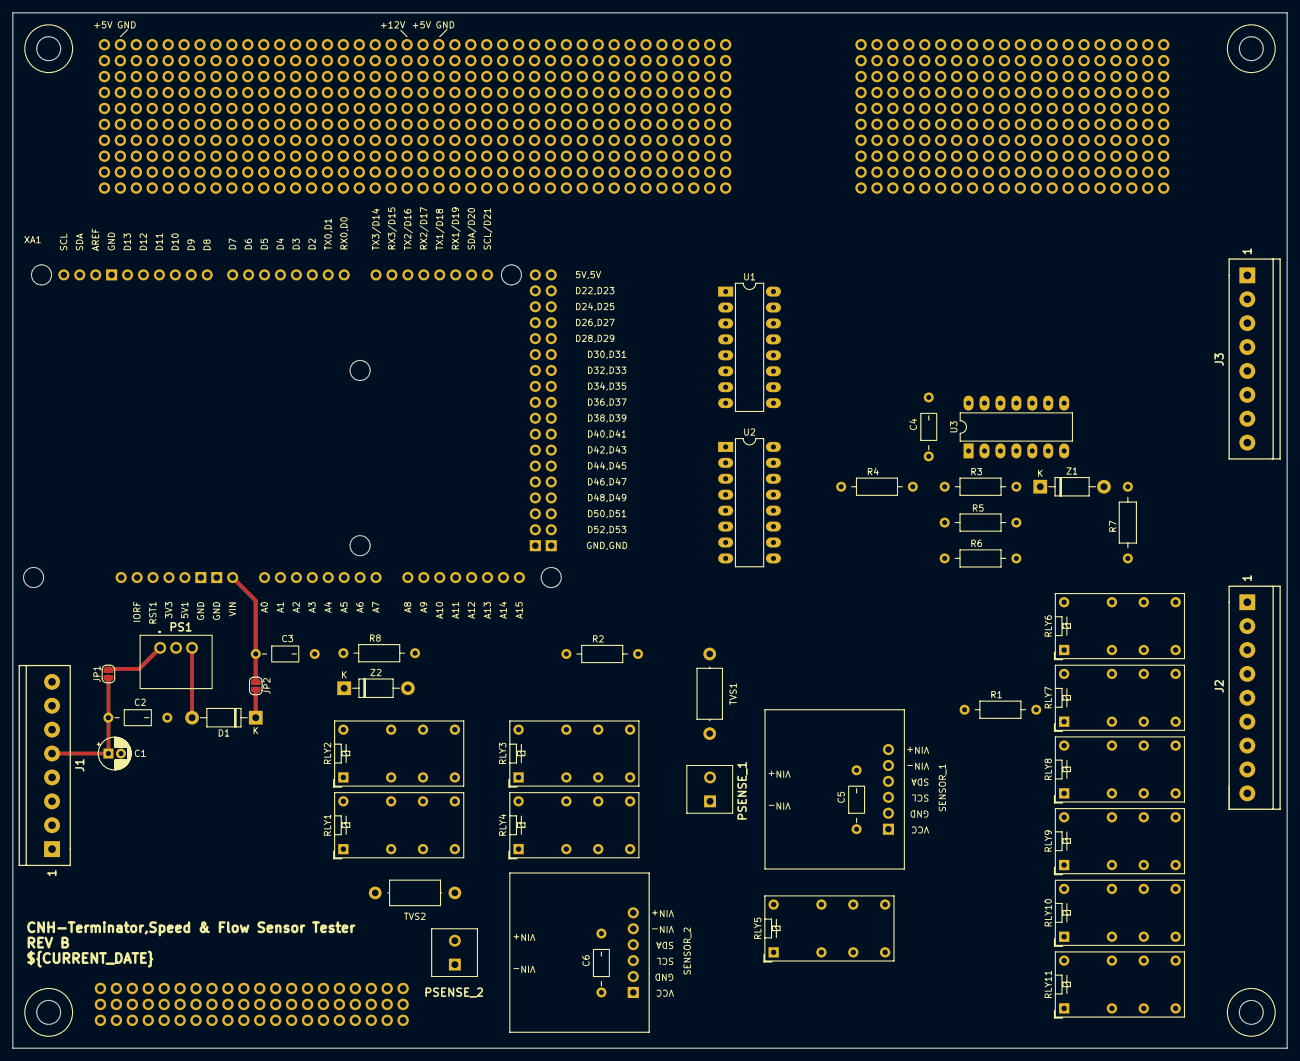
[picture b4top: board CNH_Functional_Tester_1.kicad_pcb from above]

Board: 4 copper layers, 203.2 x 165.1 mm, 81 parts (0 on the bottom side), 64 nets.

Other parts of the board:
MTH1, MTH2, MTH3, MTH4: MTH 6-32_NPTH

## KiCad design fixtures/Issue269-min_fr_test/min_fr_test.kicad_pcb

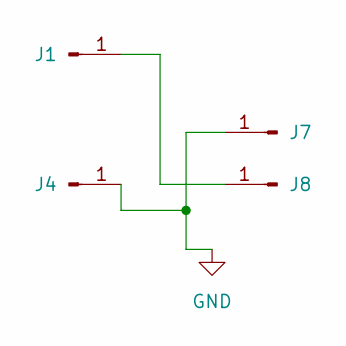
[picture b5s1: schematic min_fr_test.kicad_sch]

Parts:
J1, J4, J7, J8: Conn_01x01_Pin; TestPoint_Pad_1.0x1.0mm

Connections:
GND: J4.1, J7.1
unnamed: J1.1, J8.1

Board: 4 copper layers, 4 parts (0 on the bottom side), 2 nets, no tracks yet.
